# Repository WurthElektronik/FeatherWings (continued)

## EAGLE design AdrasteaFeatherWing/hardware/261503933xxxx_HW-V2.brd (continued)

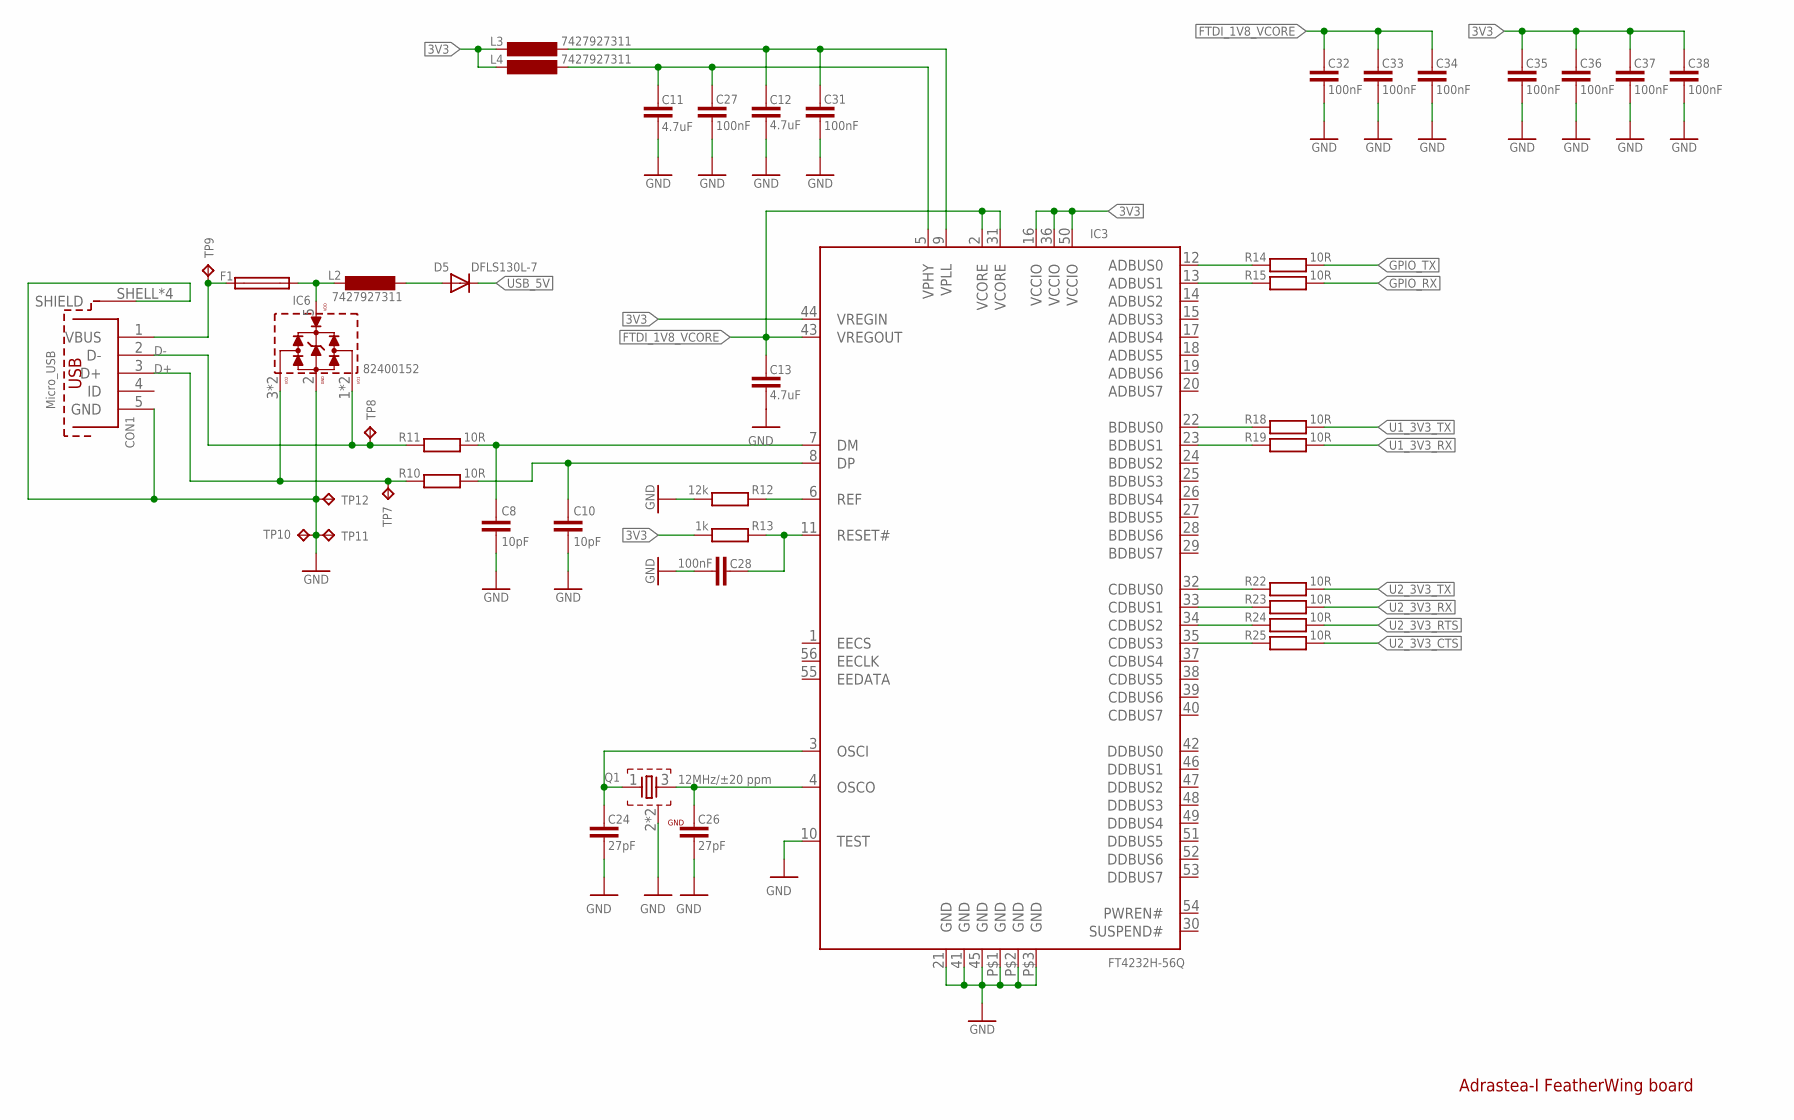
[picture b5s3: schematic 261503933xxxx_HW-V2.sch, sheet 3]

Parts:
C8, C10: 10pF; C0402_IPC
C11, C12, C13: 4.7uF; C0402_IPC
C24, C26: 27pF; C0402_IPC
C27, C28, C31, C32, C33, C34, C35, C36, C37, C38: 100nF; C0402_IPC
CON1: Micro_USB; 629105150521
D5: DFLS130L-7; SOD123_POWERDI
F1: ERB-RD1R50X; 0402
IC3: FT4232H-56Q; VQFN-56
IC6: 82400152; WE-TVS_SOT563
L2, L3, L4: 7427927311; L0402_WE-MK
Q1: 12MHz/±20 ppm; WE-XTAL_CFPX-180
R10, R11, R14, R15, R18, R19, R22, R23, R24, R25: 10R; R0402_IPC
R12: 12k; R0402_IPC
R13: 1k; R0402_IPC
TP7, TP8, TP9, TP10, TP11, TP12: TP15R

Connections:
3V3: C35.2, C36.2, C37.2, C38.2, IC3.16 (VCCIO), IC3.36 (VCCIO), IC3.44 (VREGIN), IC3.50 (VCCIO), L3.P$2 (2), L4.P$2 (2), R13.1; also elsewhere on the board
D+: CON1.3 (D+), IC6.3 (I/O2), IC6.4 (I/O2), R10.1, TP7.P$1
D-: CON1.2 (D-), IC6.1 (I/O1), IC6.6 (I/O1), R11.2, TP8.P$1
FTDI_1V8_VCORE: C13.1, C32.2, C33.2, C34.2, IC3.2 (VCORE), IC3.31 (VCORE), IC3.43 (VREGOUT)
FTDI_CTS#_CH-C: IC3.35 (CDBUS3), R25.1
FTDI_RESET: C28.2, IC3.11 (RESET#), R13.2
FTDI_RTS#_CH-C: IC3.34 (CDBUS2), R24.1
FTDI_RXD_CH-A: IC3.13 (ADBUS1), R15.1
FTDI_RXD_CH-B: IC3.23 (BDBUS1), R19.1
FTDI_RXD_CH-C: IC3.33 (CDBUS1), R23.1
FTDI_TXD_CH-A: IC3.12 (ADBUS0), R14.1
FTDI_TXD_CH-B: IC3.22 (BDBUS0), R18.1
FTDI_TXD_CH-C: IC3.32 (CDBUS0), R22.1
GND: C8.1, C10.1, C11.2, C12.2, C13.2, C24.1, C26.1, C27.1, C28.1, C31.1, C32.1, C33.1, C34.1, C35.1, C36.1, C37.1, C38.1, CON1.5 (GND), CON1.SHELL (SHIELD), CON1.SHELL1 (SHIELD), CON1.SHELL2 (SHIELD), CON1.SHELL3 (SHIELD), IC3.10 (TEST), IC3.21 (GND), IC3.41 (GND), IC3.45 (GND), IC3.P$1 (GND), IC3.P$2 (GND), IC3.P$3 (GND), IC6.2 (GND), Q1.2 (GND), Q1.4 (GND), R12.1, TP10.P$1, TP11.P$1, TP12.P$1; also elsewhere on the board
GPIO_RX: R15.2; also elsewhere on the board
GPIO_TX: R14.2; also elsewhere on the board
unnamed: C8.2, IC3.7 (DM), R11.1
unnamed: C10.2, IC3.8 (DP), R10.2
unnamed: D5.A, L2.P$1 (1)
unnamed: F1.2, IC6.5 (VDD), L2.P$2 (2)
unnamed: C11.1, C27.2, IC3.5 (VPHY), L4.P$1 (1)
unnamed: C12.1, C31.2, IC3.9 (VPLL), L3.P$1 (1)
unnamed: IC3.6 (REF), R12.2
unnamed: C24.2, IC3.3 (OSCI), Q1.1
unnamed: C26.2, IC3.4 (OSCO), Q1.3 (2)
U1_3V3_RX: R19.2; also elsewhere on the board
U1_3V3_TX: R18.2; also elsewhere on the board
U2_3V3_CTS: R25.2; also elsewhere on the board
U2_3V3_RTS: R24.2; also elsewhere on the board
U2_3V3_RX: R23.2; also elsewhere on the board
U2_3V3_TX: R22.2; also elsewhere on the board
USB_5V: D5.K (C); also elsewhere on the board
VBUS: CON1.1 (VBUS), F1.1, TP9.P$1

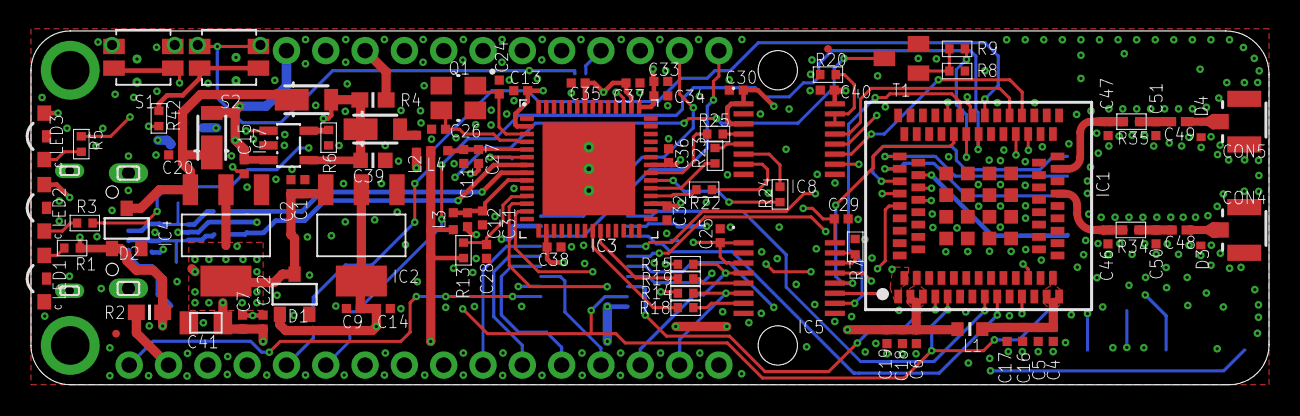
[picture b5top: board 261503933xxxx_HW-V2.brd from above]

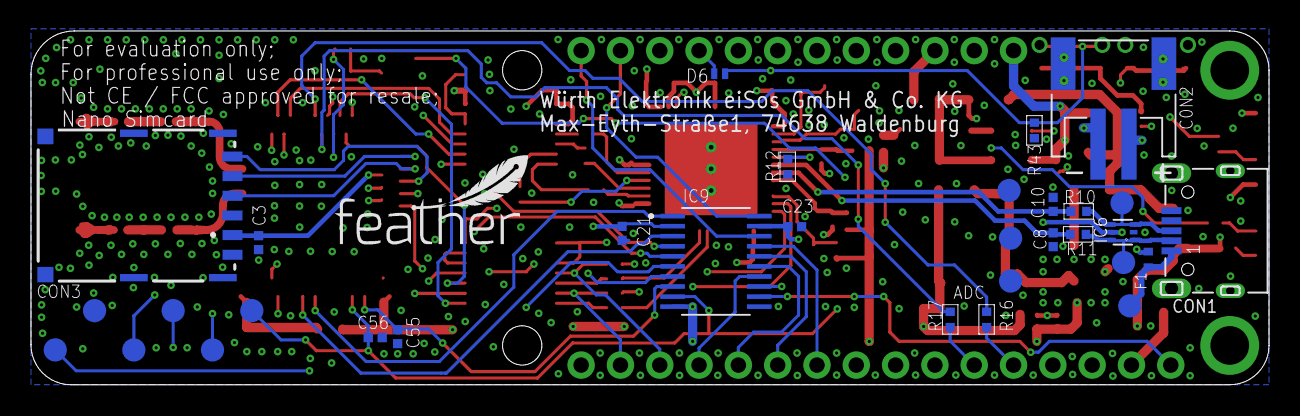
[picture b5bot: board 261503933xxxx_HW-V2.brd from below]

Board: 4 copper layers, 80.0 x 22.9 mm, 127 parts (33 on the bottom side), 91 nets.

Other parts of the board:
U$4: FEATHER_12MM

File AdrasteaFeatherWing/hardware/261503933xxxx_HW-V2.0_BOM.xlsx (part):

Part | Value | NR | MANUFACTURER | COMMENT | Device | Package | Description | CCH-TYP | COMMENT2 | DATASHEET-URL | DESCRIPTION3 | GENDER | GERDER | HEIGHT | HERSTELLER | ILEAK | ISAT | Spalte4 | MANUFACTURER2 | MAT | MF | MOUNT | MP | Spalte5 | NR2 | P | PACK | PACKAGE6 | PART-NUMBER | PINS | PRICE | RDC | SPG | TEMP | TOL | TYPE | VALUE | VCH-TYP | VESD-AIR | VESD-CONTACT | Z
C0N2 | LiPoLy-Plug | 1769 | Adafruit |  | JST_2PIN | JST-PH-2-SMT-RA-ADRASTEA-ANGEPASST | JST 2-Pin Connectors of various flavors |  |  |  |  |  |  | 9mm |  |  |  |  |  |  |  |  |  |  |  |  | SMT
C1 | 100nF | 885012205037 | Würth Elektronik |  | C0402_IPC | C0402_IPC |  |  |  |  |  |  |  | 0.5mm |  |  |  |  |  | X7R |  |  |  |  |  |  | 402 |  |  |  |  |  | 16V |  | 0.1
C10 | 10pF | 885012005055 | Würth Elektronik |  | C10PF0402_IPC | C0402_IPC |  |  |  |  |  |  |  | 0.5mm |  |  |  |  |  | NP0 |  |  |  |  |  |  | 402 |  |  |  |  |  | 50V |  | 0.05
C11 | 4.7uF | 885012105008 | Würth Elektronik |  | C4.7UF0402_IPC | C0402_IPC |  |  |  |  |  |  |  | 0.5mm |  |  |  |  |  | X5R |  |  |  |  |  |  | 402 |  |  |  |  |  | 6.3V |  | 0.2
C12 | 4.7uF | 885012105008 | Würth Elektronik |  | C4.7UF0402_IPC | C0402_IPC |  |  |  |  |  |  |  | 0.5mm |  |  |  |  |  | X5R |  |  |  |  |  |  | 402 |  |  |  |  |  | 6.3V |  | 0.2
C13 | 4.7uF | 885012105008 | Würth Elektronik |  | C4.7UF0402_IPC | C0402_IPC |  |  |  |  |  |  |  | 0.5mm |  |  |  |  |  | X5R |  |  |  |  |  |  | 402 |  |  |  |  |  | 6.3V |  | 0.2
C14 | 100nF | 885012205037 | Würth Elektronik |  | C0402_IPC | C0402_IPC |  |  |  |  |  |  |  | 0.5mm |  |  |  |  |  | X7R |  |  |  |  |  |  | 402 |  |  |  |  |  | 16V |  | 0.1
C15 | 10uF | 885012105020 | Würth Elektronik |  | C10UF0402_IPC | C0402_IPC |  |  |  |  |  |  |  | 0.5mm |  |  |  |  |  | X5R |  |  |  |  |  |  | 402 |  |  |  |  |  | 6.3V | -55 to +85°c | 0.2
C16 | 10uF | 885012105020 | Würth Elektronik |  | C0402_IPC | C0402_IPC |  |  |  |  |  |  |  | 0.5mm |  |  |  |  |  | X5R | 0.2 |  |  |  |  |  | 402 |  |  |  |  |  | 6,3V |  | 0.2
C17 | 1uF | 885012105012 | Würth Elektronik |  | C1UF0402_IPC | C0402_IPC |  |  |  |  |  |  |  | 0.5mm |  |  |  |  |  | X5R |  |  |  |  |  |  | 402 |  |  |  |  |  | 10V |  | 0.2
C18 | 10uF | 885012105020 | Würth Elektronik |  | C0402_IPC | C0402_IPC |  |  |  |  |  |  |  | 0.5mm |  |  |  |  |  | X5R | 0.2 |  |  |  |  |  | 402 |  |  |  |  |  | 6,3V |  | 0.2
C19 | 10uF | 885012105020 | Würth Elektronik |  | C0402_IPC | C0402_IPC |  |  |  |  |  |  |  | 0.5mm |  |  |  |  |  | X5R | 0.2 |  |  |  |  |  | 402 |  |  |  |  |  | 6,3V |  | 0.2
C2 | 1uF | 885012105012 | Würth Elektronik |  | C1UF0402_IPC | C0402_IPC |  |  |  |  |  |  |  | 0.5mm |  |  |  |  |  | X5R |  |  |  |  |  |  | 402 |  |  |  |  |  | 10V |  | 0.2
C20 | 100nF | 885012205037 | Würth Elektronik |  | C0402_IPC | C0402_IPC |  |  |  |  |  |  |  | 0.5mm |  |  |  |  |  | X7R |  |  |  |  |  |  | 402 |  |  |  |  |  | 16V |  | 0.1
C21 | 100nF | 885012205037 | Würth Elektronik |  | C0402_IPC | C0402_IPC |  |  |  |  |  |  |  | 0.5mm |  |  |  |  |  | X7R |  |  |  |  |  |  | 402 |  |  |  |  |  | 16V |  | 0.1
C22 | 100nF | 885012205037 | Würth Elektronik |  | C0402_IPC | C0402_IPC |  |  |  |  |  |  |  | 0.5mm |  |  |  |  |  | X7R |  |  |  |  |  |  | 402 |  |  |  |  |  | 16V |  | 0.1
C23 | 100nF | 885012205037 | Würth Elektronik |  | C0402_IPC | C0402_IPC |  |  |  |  |  |  |  | 0.5mm |  |  |  |  |  | X7R |  |  |  |  |  |  | 402 |  |  |  |  |  | 16V |  | 0.1
C24 | 27pF | CL05C270JB5NNNC | Samsung |  | C27P0402_IPC | C0402_IPC |  |  |  |  |  |  |  | 0.5mm |  |  |  |  |  | C0G |  |  |  |  |  |  | 402 |  |  |  |  |  | 50V |  | 0.05
C25 | 100nF | 885012205037 | Würth Elektronik |  | C0402_IPC | C0402_IPC |  |  |  |  |  |  |  | 0.5mm |  |  |  |  |  | X7R |  |  |  |  |  |  | 402 |  |  |  |  |  | 16V |  | 0.1
C26 | 27pF | CL05C270JB5NNNC | Samsung |  | C27P0402_IPC | C0402_IPC |  |  |  |  |  |  |  | 0.5mm |  |  |  |  |  | C0G |  |  |  |  |  |  | 402 |  |  |  |  |  | 50V |  | 0.05
C27 | 100nF | 885012205037 | Würth Elektronik |  | C0402_IPC | C0402_IPC |  |  |  |  |  |  |  | 0.5mm |  |  |  |  |  | X7R |  |  |  |  |  |  | 402 |  |  |  |  |  | 16V |  | 0.1
C28 | 100nF | 885012205037 | Würth Elektronik |  | C0402_IPC | C0402_IPC |  |  |  |  |  |  |  | 0.5mm |  |  |  |  |  | X7R |  |  |  |  |  |  | 402 |  |  |  |  |  | 16V |  | 0.1
C29 | 100nF | 885012205037 | Würth Elektronik |  | C0402_IPC | C0402_IPC |  |  |  |  |  |  |  | 0.5mm |  |  |  |  |  | X7R |  |  |  |  |  |  | 402 |  |  |  |  |  | 16V |  | 0.1
C3 | 100nF | 885012205037 | Würth Elektronik |  | C100NF0402_IPC | C0402_IPC |  |  |  |  |  |  |  | 0.5mm |  |  |  |  |  | X7R |  |  |  |  |  |  | 402 |  |  |  |  |  | 16V | -55 to +125°C | 0.1
C30 | 100nF | 885012205037 | Würth Elektronik |  | C0402_IPC | C0402_IPC |  |  |  |  |  |  |  | 0.5mm |  |  |  |  |  | X7R |  |  |  |  |  |  | 402 |  |  |  |  |  | 16V |  | 0.1
C31 | 100nF | 885012205037 | Würth Elektronik |  | C0402_IPC | C0402_IPC |  |  |  |  |  |  |  | 0.5mm |  |  |  |  |  | X7R |  |  |  |  |  |  | 402 |  |  |  |  |  | 16V |  | 0.1
C32 | 100nF | 885012205037 | Würth Elektronik |  | C0402_IPC | C0402_IPC |  |  |  |  |  |  |  | 0.5mm |  |  |  |  |  | X7R |  |  |  |  |  |  | 402 |  |  |  |  |  | 16V |  | 0.1
C33 | 100nF | 885012205037 | Würth Elektronik |  | C0402_IPC | C0402_IPC |  |  |  |  |  |  |  | 0.5mm |  |  |  |  |  | X7R |  |  |  |  |  |  | 402 |  |  |  |  |  | 16V |  | 0.1
C34 | 100nF | 885012205037 | Würth Elektronik |  | C0402_IPC | C0402_IPC |  |  |  |  |  |  |  | 0.5mm |  |  |  |  |  | X7R |  |  |  |  |  |  | 402 |  |  |  |  |  | 16V |  | 0.1
C35 | 100nF | 885012205037 | Würth Elektronik |  | C0402_IPC | C0402_IPC |  |  |  |  |  |  |  | 0.5mm |  |  |  |  |  | X7R |  |  |  |  |  |  | 402 |  |  |  |  |  | 16V |  | 0.1
C36 | 100nF | 885012205037 | Würth Elektronik |  | C0402_IPC | C0402_IPC |  |  |  |  |  |  |  | 0.5mm |  |  |  |  |  | X7R |  |  |  |  |  |  | 402 |  |  |  |  |  | 16V |  | 0.1
C37 | 100nF | 885012205037 | Würth Elektronik |  | C0402_IPC | C0402_IPC |  |  |  |  |  |  |  | 0.5mm |  |  |  |  |  | X7R |  |  |  |  |  |  | 402 |  |  |  |  |  | 16V |  | 0.1
C38 | 100nF | 885012205037 | Würth Elektronik |  | C0402_IPC | C0402_IPC |  |  |  |  |  |  |  | 0.5mm |  |  |  |  |  | X7R |  |  |  |  |  |  | 402 |  |  |  |  |  | 16V |  | 0.1
C39 | 10uF | 885012106031 | Wurth Elektronik |  | C1UF0603_IPC | C0603_IPC |  |  |  |  |  |  |  | 0.8mm |  |  |  |  |  | X5R |  |  |  |  |  |  | 603 |  |  |  |  |  | 25V |  | 0.1
C4 | 100nF | 885012205037 | Würth Elektronik |  | C0402_IPC | C0402_IPC |  |  |  |  |  |  |  | 0.5mm |  |  |  |  |  | X7R |  |  |  |  |  |  | 402 |  |  |  |  |  | 16V |  | 0.1
C40 | 100nF | 885012205037 | Würth Elektronik |  | C0402_IPC | C0402_IPC |  |  |  |  |  |  |  | 0.5mm |  |  |  |  |  | X7R |  |  |  |  |  |  | 402 |  |  |  |  |  | 16V |  | 0.1
C41 | 47µF | 885012107006 | Wurth Elektronik |  | C47UF0805 | C0805 |  |  |  |  |  |  |  | 1.25mm |  |  |  |  |  | X7R |  |  |  |  |  |  | 805 |  |  |  |  |  | 6.3V |  | 0.2
C46 | n.m. | n.m. | n.m. |  | C0402_IPC | C0402_IPC |  |  |  |  |  |  |  | 0.5mm |  |  |  |  |  |  |  |  |  |  |  |  | 402
C47 | n.m. | n.m. | n.m. |  | C0402_IPC | C0402_IPC |  |  |  |  |  |  |  | 0.5mm |  |  |  |  |  |  |  |  |  |  |  |  | 402
C48 | 100pF | 885012005061 | Würth Elektronik |  | C100PF0402_IPC | C0402_IPC |  |  |  |  |  |  |  | 0.5mm |  |  |  |  |  | NP0 |  |  |  |  |  |  | 402 |  |  |  |  |  | 50V |  | 0.05
C49 | 100pF | 885012005061 | Würth Elektronik |  | C0402_IPC | C0402_IPC |  |  |  |  |  |  |  | 0.5mm |  |  |  |  |  | NP0 |  |  |  |  |  |  | 402 |  |  |  |  |  | 50V |  | 0.05
C5 | 10uF | 885012105020 | Würth Elektronik |  | C0402_IPC | C0402_IPC |  |  |  |  |  |  |  | 0.5mm |  |  |  |  |  | X5R | 0.2 |  |  |  |  |  | 402 |  |  |  |  |  | 6,3V |  | 0.2
C50 | n.m. | n.m. | n.m. |  | C0402_IPC | C0402_IPC |  |  |  |  |  |  |  | 0.5mm |  |  |  |  |  |  |  |  |  |  |  |  | 402
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
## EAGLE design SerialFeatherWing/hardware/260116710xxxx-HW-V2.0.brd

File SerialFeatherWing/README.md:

# Serial FeatherWing

## Introduction

The Würth Elektronik eiSos Serial bridge FeatherWing is a development board that acts as an bridge between UART and RS232/RS485/RS422. It is fully compatible to the popular [Adafruit](https://www.adafruit.com/) [Feather line](https://www.adafruit.com/feather) of development boards and can be used as plug-and-play solution to connect any D-SUB9 interfaced device to the Feather ecosystem.

This FeatherWing acts as a bridge between legacy RS232/RS485 devices and modern wired/wireless digital interfaces
### Key Features

* 3V3 logic level UART interface on the Feather pin header.
* Support to 5V logic level
* RS232 with and without flow control
* Full and half duplex RS485
* Double throw slider to switch between RS232 and RS485

This repository contains the [Eagle](https://www.autodesk.com/products/eagle/overview) design files for the MagI³C Power FeatherWing [PCB](hardware).

Feel free to check our [YouTube channel](https://www.youtube.com/user/WuerthElektronik/videos) for video tutorials, hands-ons and webinars relating to our products.

## Hardware

### Description

The Serial FeatherWing was designed with rapid prototyping in mind. Being fully compatible with the Adafruit ecosystem, this FeatherWing gives the user the flexibility to choose the preferred host microcontroller. The inherent modularity of the ecosystem allows the FeatherWing to be easily integrated into any project.

### Connectors

#### CON1
This is a standard D-subminiature Male connector. The pinout for different modes of operation are as described in the table below.

|Pin | RS232 | RS485(Full Duplex)| RS485 (Half Duplex)|
|----|----------|-------------|------|
|1| Not connected |Not connected| Not connected|
|2 |RX |RX+| Not connected|
3| TX |TX- | D-|
|4 |Not connected| Not connected| Not connected|
|5 |GND |GND |GND|
|6 |Not connected| Not connected |Not connected|
|7 |RTS| TX+ |D+|
|8 |CTS |RX-| Not connected|
|9 |Not connected| Not connected |Not connected|

#### Feather Connector
This is the standard set of connectors that is used across the Feather ecosystem. The table below describes the functions of each of the 28 pins as applicable to this FeatherWing.

| Pin number | Pin name | Function |
| ------- | ------- |----------------|
|   1          |<span style="text-decoration:overline">RST</span> | Not connected|
|    2          | 3V3| 3.3 V power supply|
|    3          | AREF| Not connected|
|    4          | GND| Ground|
|    5          | A0| Not connected|
|    6          | A1| Not connected|
|    7          | A2| Not connected|
|    8          | A3| Not connected|
|    9          | A4| Not connected|
|    10         | A5| Not connected|
|    11         | SCK| Not connected|
|    12         | MOSI| Not connected|
|    13         | MISO| Not connected|
|    14         | U0RX| Connected to UART TX(RS232/RS485 TX)|
|    15         | U0TX| Connected to UART RX(RS232/RS485 RX)|
|    16         | NC| Not connected|

| Pin number | Pin name | Function |
| ------- | ------- |----------------|
|    17         | SDA| Not connected|
|    18         | SCL| Not connected|
|    19         | 5| Not connected|
|    20         | 6| Not connected|
|    21         | 9| Not connected|
|    22         | U1TX|(optional) Connected to UART RX(RS232 RS485 RX)|
|    23         | U1RX|(optional) Connected to UART TX(RS232/RS485 TX)|
|    24         | 12| Not connected|
|    25         | 13| Not connected|
|    26         | 5V| 5 V Power supply|
|    27         | EN| Not connected|
|    28         | VBAT| Not connected| 

### Switches

#### Switch S1

This sliding switch can be used to select between the two input signal options, RS232 or RS485.
|Position| Mode|
|--------|------|
|Top (Away from D-SUB 9 connector)| RS232|
|Bottom (Towards D-SUB 9 connector)| RS485|

#### Switch S2

This sliding switch determines if the RX/TX lines are crossed to connect directly to another UART peripheral such as a radio module.
|Position| Mode|
|--------|------|
|Top (Away from D-SUB 9 connector)| TX and RX are crossed|
|Bottom (Towards D-SUB 9 connector)| TX and RX are not crossed|

### Jumpers

#### Jumper JP1

This jumper enables switching between half and full duplex modes as well as enabling/disabling the slew rate.

|Connection| Mode|
|--------|-------|
|1-3| Full duplex|
|3-5|Half duplex|

|Connection| Mode|
|--------|-------|
|2-4 |Slew rate enabled|
|4-6 |Slew rate disabled|

#### Jumper JP2

This jumper enables switching between the UART0 and UART1 on the feather connector.

|Connection| Mode|
|--------|-------|
|1-3 and 2-4| UART0|
|3-5 and 4-6|UART1|

#### Jumper JP3
This jumper enables connecting the flow control pins to the GPIOs on the feather connector

|Connection| Mode|
|--------|-------|
|1-2| RTS/DE connected to GPIO12|
|3-4|CTS conected to GPIO13|

### Schematics
The hardware design files including the schematics can be found in the [hardware folder](hardware).

### DISCLAIMER:
THE USE OF THE WÜRTH ELEKTRONIK EISOS DESIGN EXAMPLE / REFERENCE DESIGN IS ENTIRELY AT YOUR OWN RISK. IT IS YOUR SOLE RESPONSIBILITY TO IMPLEMENT THE DESIGN EXAMPLE / REFERENCE DESIGN WITH ALL TECHNICAL AND REGULATORY REQUIREMENTS IN YOUR APPLICATION. IT IS ALSO YOUR RESPONSIBILITY TO VERIFY THE FUNCTION AND PERFORMANCE OF YOUR DESIGN IN YOUR OWN PARTICULAR ENGINEERING AND PRODUCT ENVIRONMENT AND YOU ASSUME THE ENTIRE RISK OF DOING SO OR FAILING TO DO SO. THE WÜRTH ELEKTRONIK EISOS DESIGN EXAMPLE / REFERENCE DESIGN IS PROVIDED ON AN "AS IS" OR "AS AVAILABLE" BASIS, WITHOUT ANY WARRANTIES OF ANY KIND AND WÜRTH ELEKTRONIK EISOS DISCLAIMS ANY WARRANTIES EXPRESS OR IMPLIED, INCLUDING WITHOUT LIMITATION THE MERCHANTABILITY OR FITNESS FOR A PARTICULAR PURPOSE, USAGE OR THE NON-INFRINGEMENT OF THIRD PARTIES’ INTELLECTUAL PROPERTY RIGHTS. NO LICENSE IS GRANTED TO ANY INTELLECTUAL PROPERTY RIGHT BY WÜRTH ELEKTRONIK EISOS OR ANY THIRD PARY. UNDER NO CIRCUMSTANCES SHALL WÜRTH ELEKTRONIK EISOS BE LIABLE FOR DAMAGES INCURRED BY REASON OF OTHER SERVICES OR PRODUCTS RECEIVED THROUGH OR ADVERTISED IN CONNECTION WITH THE WÜRTH ELEKTRONIK EISOS SITE OR THE WÜRTH ELEKTRONIK EISOS DESIGN EXAMPLE / REFERENCE DESIGN. THE WÜRTH ELEKTRONIK EISOS DESIGN EXAMPLE / REFERENCE DESIGN IS SUBJECT TO CHANGE WITHOUT NOTICE.

## Software
Serial bridge FeatherWing **software examples** can be found in the [software folder](software).

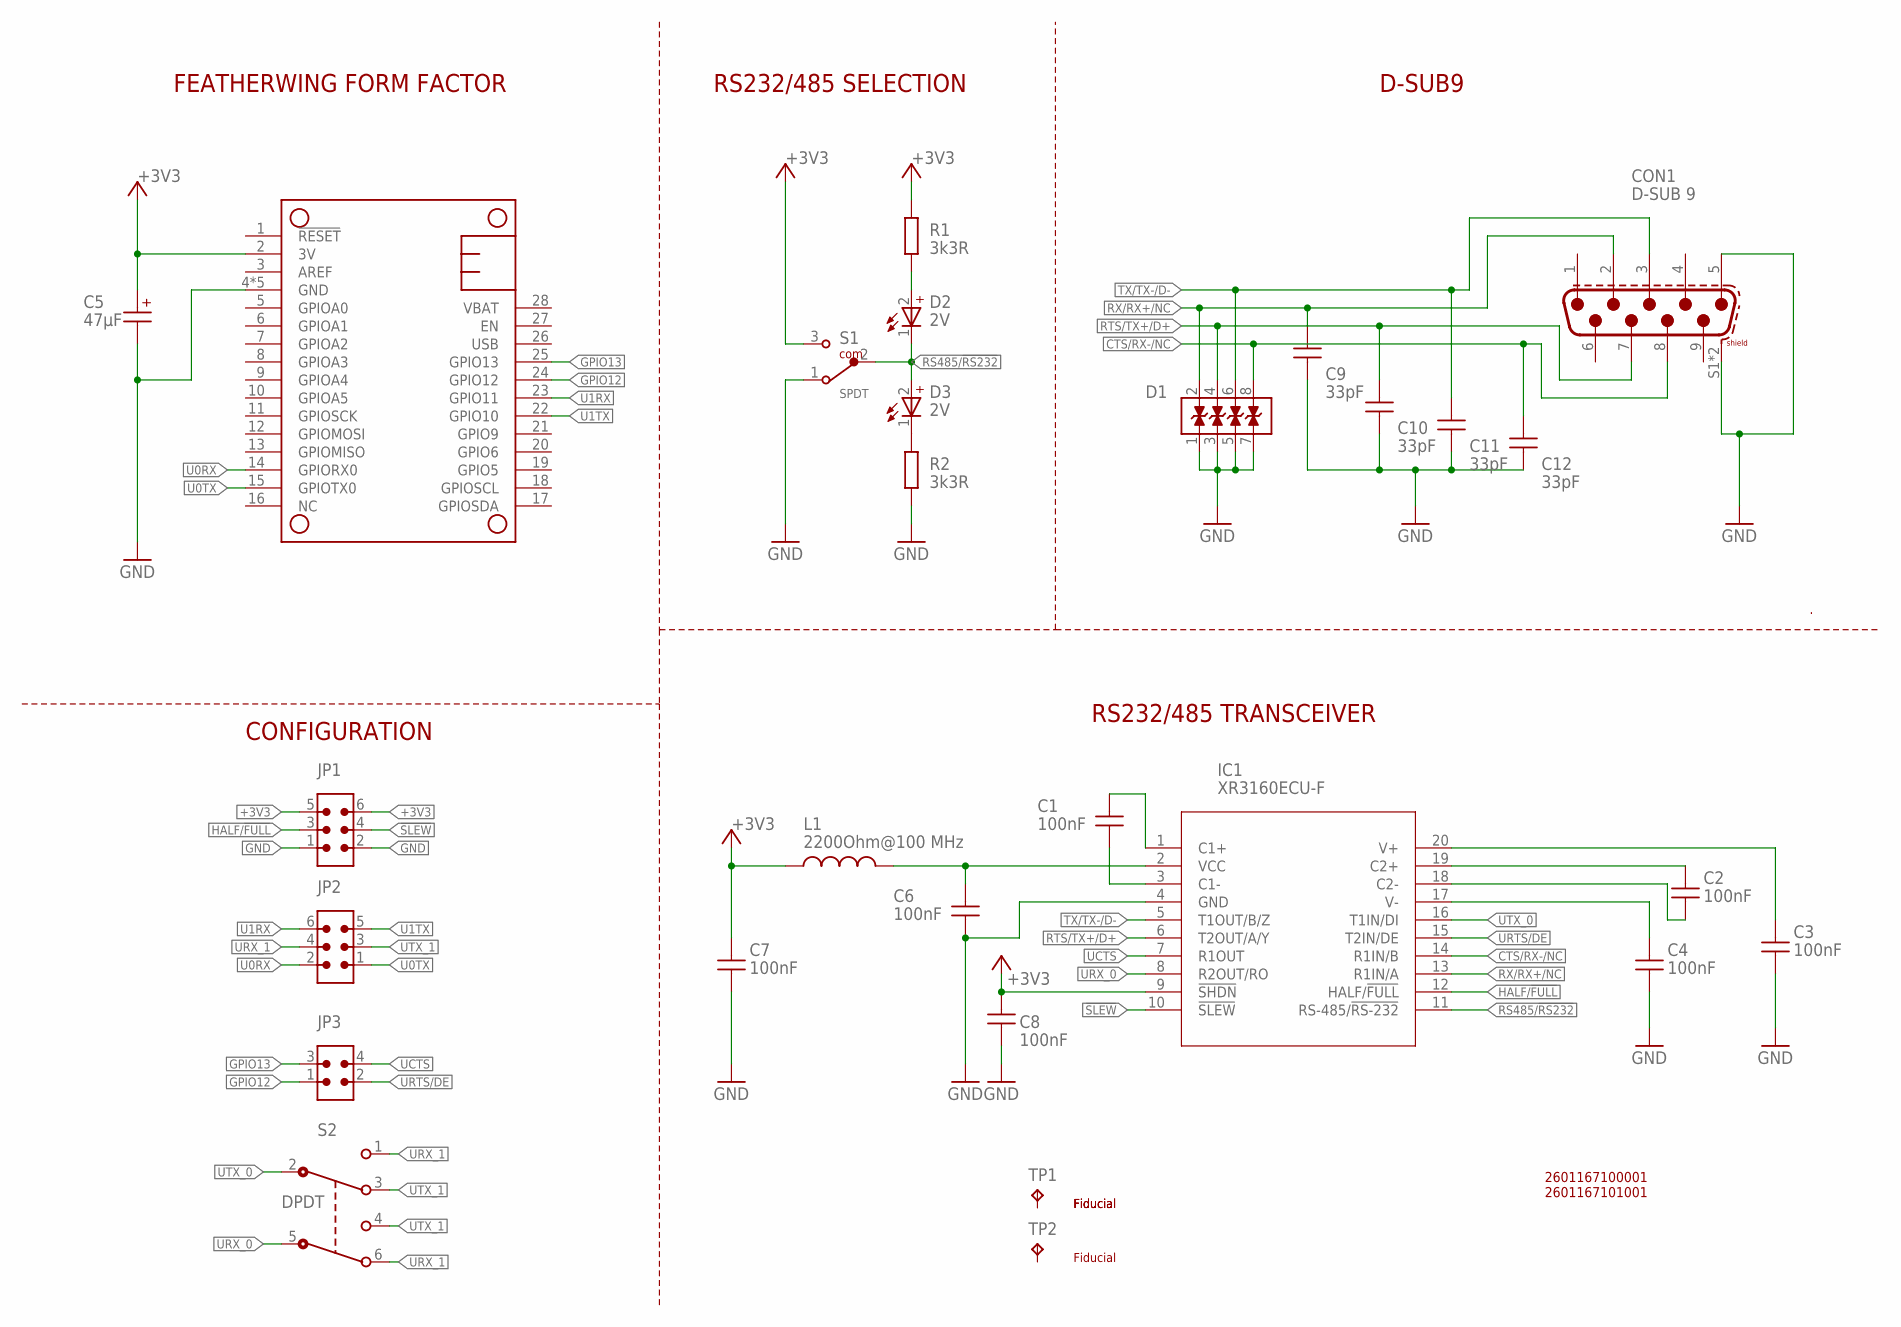
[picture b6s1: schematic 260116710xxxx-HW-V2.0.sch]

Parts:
C1, C2, C3, C4, C6, C7, C8: 100nF; WCAP-CSGP_0603_W
C5: 47µF; WCAP-AS5H_5X5.5(DXL)
C9, C10, C11, C12: 33pF; WCAP-CSGP_0603_W
CON1: D-SUB 9; 618009231221
D1: 18V; WE-VEA_0612
D2, D3: 2V; WL-SMCW_0603
IC1: XR3160ECU-F; SSOP-20
JP1, JP2: 61300621121
JP3: 61300421121
L1: 2200Ohm@100 MHz; WE-CBF_0603(W=2.2)
MS1: FEATHERWING_WIDE; PART-NUMBER 2830
R1, R2: 3k3R; R0603
S1: SPDT; 450404015514
S2: DPDT; 452403012014
TP1, TP2: TPB1,27; B1,27

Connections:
!SLEW: IC1.10 (!SLEW), JP1.4
+3V3: C5.1 (+), C7.2, C8.2, IC1.9 (!SHDN), JP1.5, JP1.6, L1.2, MS1.2 (3V), R1.1, S1.3
CTS/RX-/NC: C12.1, CON1.8, D1.8 (5), IC1.14 (R1IN/B)
GND: C3.1, C4.1, C5.2 (-), C6.1, C7.1, C8.1, C9.2, C10.2, C11.2, C12.2, CON1.5, CON1.S1 (SHIELD), CON1.S2 (SHIELD), D1.1, D1.3 (2), D1.5 (3), D1.7 (4), IC1.4 (GND), JP1.1, JP1.2, MS1.4 (GND), MS1.GND@0 (GND), MS1.GND@1 (GND), MS1.GND@2 (GND), MS1.GND@3 (GND), R2.1, S1.1
GPIO12: JP3.1, MS1.24 (GPIO12)
GPIO13: JP3.3, MS1.25 (GPIO13)
HALF/!FULL: IC1.12 (HALF/!FULL), JP1.3
unnamed: D3.1 (-), R2.2
unnamed: D2.2 (+), R1.2
unnamed: C1.2, IC1.1 (C1+)
unnamed: C1.1, IC1.3 (C1-)
unnamed: C6.2, IC1.2 (VCC), L1.1
unnamed: C2.2, IC1.19 (C2+)
unnamed: C2.1, IC1.18 (C2-)
unnamed: C3.2, IC1.20 (V+)
unnamed: C4.2, IC1.17 (V-)
RS485/!RS232: D2.1 (-), D3.2 (+), IC1.11 (RS-485/!RS-232), S1.2
RTS/TX+/D+: C10.1, CON1.7, D1.4 (7), IC1.6 (T2OUT/A/Y)
RX/RX+/NC: C9.1, CON1.2, D1.2 (8), IC1.13 (R1IN/A)
TX/TX-/D-: C11.1, CON1.3, D1.6, IC1.5 (T1OUT/B/Z)
U0RX: JP2.2, MS1.14 (GPIORX0)
U0TX: JP2.1, MS1.15 (GPIOTX0)
U1RX: JP2.6, MS1.23 (GPIO11)
U1TX: JP2.5, MS1.22 (GPIO10)
UCTS: IC1.7 (R1OUT), JP3.4
URTS/DE: IC1.15 (T2IN/DE), JP3.2
URX_0: IC1.8 (R2OUT/RO), S2.5
URX_1: JP2.4, S2.1, S2.6
UTX_0: IC1.16 (T1IN/DI), S2.2
UTX_1: JP2.3, S2.3, S2.4

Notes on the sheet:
FEATHERWING FORM FACTOR
CONFIGURATION
RS232/485 SELECTION
D-SUB9
RS232/485 TRANSCEIVER
2601167100001 2601167101001
Fiducial

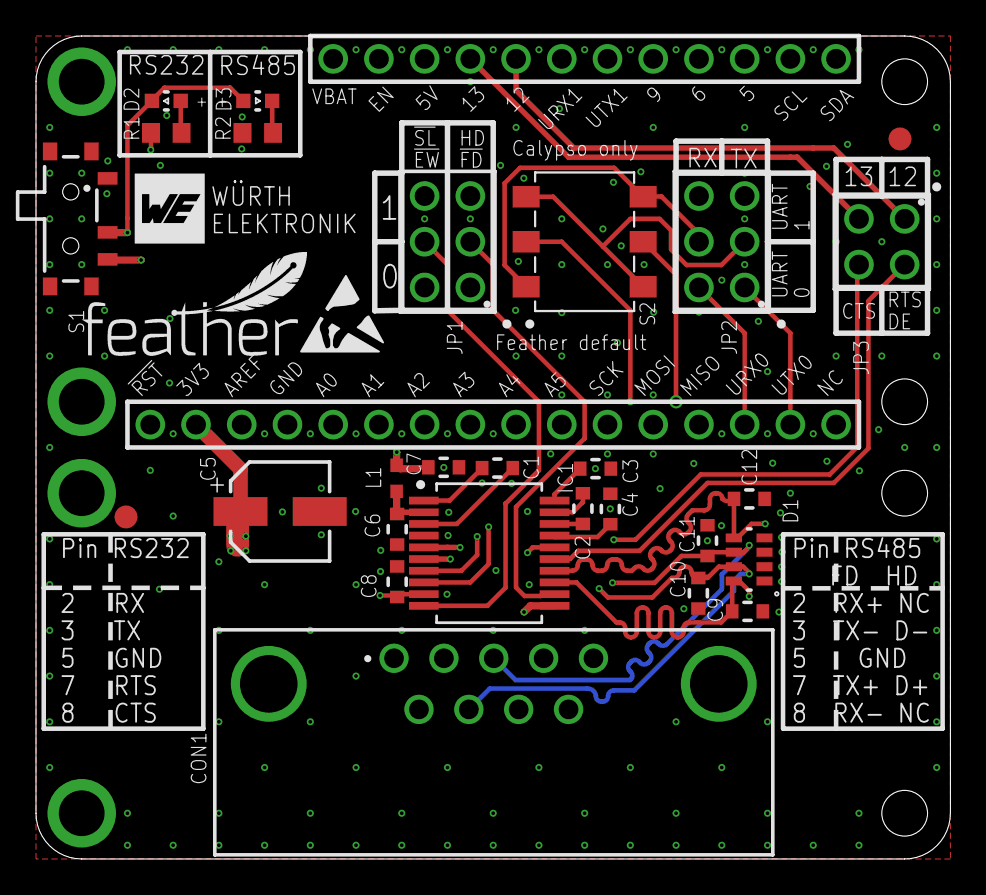
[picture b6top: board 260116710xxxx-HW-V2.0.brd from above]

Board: 4 copper layers, 50.8 x 45.7 mm, 32 parts (1 on the bottom side), 30 nets.

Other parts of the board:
U$1: WE-NEW_SKELETON_4MM
U$2: WE-NEW_SKELETON_8MM
U$4: ESD_5MM
U$5: FEATHER_12MM

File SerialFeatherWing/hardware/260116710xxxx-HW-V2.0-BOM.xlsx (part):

Part | Value | NR | MANUFACTURER | Device | Package | Description | ABSTRAHLWINKEL | CERAMIC-TYPE | CHANNELS | CHIP-TECHNOLOGY | COMMENT | COPYRIGHT | DATASHEET-URL | DF | DIAMETER | DIGI-KEY_PART_NUMBER_1 | EMITTING-COLOR | GENDER | HEIGHT | I-LEAK | I-RIPPLE | I-V-TYP | ILEAK | IR | IR2 | L | LAMDA-DOM-TYP | LAMDA-PEAK-TYP | MANUFACTURER_PART_NUMBER | MATES-WITH | MFR_NAME | PACK | OPERATING-TEMPERATURE | PACK | PACKAGING | PINS | PITCH | PQ | QMIN | QTY | RDC-MAX | RISO | ROWS | TECHNICAL-REFERENCE | TOL-VALUE | TP_SIGNAL_NAME | TYPE | V-F-TYP | VALUE | VR | WE-NUMBER | Z | Z-MAX | TOL
C1 | 100 nF | 885012206020 | Wurth Elektronik | WCAP-CSGP_0603_885012206020_10V(DC)_W | WCAP-CSGP_0603_W | WCAP-CSGP MLCCs 0603 |  | X7R Class II |  |  |  |  | https://www.we-online.com/catalog/datasheet/885012206020.pdf | 0.05 |  |  |  |  | 0.8mm |  |  |  |  |  |  |  |  |  |  |  |  | SMT | -55 °C up to +125 °C |  |  |  |  |  | - |  |  | 5GOhm |  | X7R0603104K010DFCT10000 | ±10% |  |  |  | 100 nF | 10V(DC)
C2 | 100 nF | 885012206020 | Wurth Elektronik | WCAP-CSGP_0603_885012206020_10V(DC)_W | WCAP-CSGP_0603_W | WCAP-CSGP MLCCs 0603 |  | X7R Class II |  |  |  |  | https://www.we-online.com/catalog/datasheet/885012206020.pdf | 0.05 |  |  |  |  | 0.8mm |  |  |  |  |  |  |  |  |  |  |  |  | SMT | -55 °C up to +125 °C |  |  |  |  |  | - |  |  | 5GOhm |  | X7R0603104K010DFCT10000 | ±10% |  |  |  | 100 nF | 10V(DC)
C3 | 100 nF | 885012206020 | Wurth Elektronik | WCAP-CSGP_0603_885012206020_10V(DC)_W | WCAP-CSGP_0603_W | WCAP-CSGP MLCCs 0603 |  | X7R Class II |  |  |  |  | https://www.we-online.com/catalog/datasheet/885012206020.pdf | 0.05 |  |  |  |  | 0.8mm |  |  |  |  |  |  |  |  |  |  |  |  | SMT | -55 °C up to +125 °C |  |  |  |  |  | - |  |  | 5GOhm |  | X7R0603104K010DFCT10000 | ±10% |  |  |  | 100 nF | 10V(DC)
C4 | 100 nF | 885012206020 | Wurth Elektronik | WCAP-CSGP_0603_885012206020_10V(DC)_W | WCAP-CSGP_0603_W | WCAP-CSGP MLCCs 0603 |  | X7R Class II |  |  |  |  | https://www.we-online.com/catalog/datasheet/885012206020.pdf | 0.05 |  |  |  |  | 0.8mm |  |  |  |  |  |  |  |  |  |  |  |  | SMT | -55 °C up to +125 °C |  |  |  |  |  | - |  |  | 5GOhm |  | X7R0603104K010DFCT10000 | ±10% |  |  |  | 100 nF | 10V(DC)
C5 | 47µF | 865230142003 | Wurth Elektronik | WCAP-AS5H_5X5.5_865230142003 | WCAP-AS5H_5X5.5(DXL) | WCAP-AS5H Aluminium Electrolytic Capacitors |  |  |  |  |  |  | https://www.we-online.com/catalog/datasheet/865230142003.pdf | 0.32 | 5mm |  |  |  |  | 3uA | 36mA |  |  |  |  | 5.5mm |  |  |  |  |  | SMT | -40 °C up to +105 °C |  |  |  |  |  |  |  |  |  |  | ASDC055470M6R3DVCTBE000 |  |  |  |  | 47 µF | 6.3V(DC) |  | 1.61882Ohm
C6 | 100 nF | 885012206020 | Wurth Elektronik | WCAP-CSGP_0603_885012206020_10V(DC)_W | WCAP-CSGP_0603_W | WCAP-CSGP MLCCs 0603 |  | X7R Class II |  |  |  |  | https://www.we-online.com/catalog/datasheet/885012206020.pdf | 0.05 |  |  |  |  | 0.8mm |  |  |  |  |  |  |  |  |  |  |  |  | SMT | -55 °C up to +125 °C |  |  |  |  |  | - |  |  | 5GOhm |  | X7R0603104K010DFCT10000 | ±10% |  |  |  | 100 nF | 10V(DC)
C7 | 100 nF | 885012206020 | Wurth Elektronik | WCAP-CSGP_0603_885012206020_10V(DC)_W | WCAP-CSGP_0603_W | WCAP-CSGP MLCCs 0603 |  | X7R Class II |  |  |  |  | https://www.we-online.com/catalog/datasheet/885012206020.pdf | 0.05 |  |  |  |  | 0.8mm |  |  |  |  |  |  |  |  |  |  |  |  | SMT | -55 °C up to +125 °C |  |  |  |  |  | - |  |  | 5GOhm |  | X7R0603104K010DFCT10000 | ±10% |  |  |  | 100 nF | 10V(DC)
C8 | 100 nF | 885012206020 | Wurth Elektronik | WCAP-CSGP_0603_885012206020_10V(DC)_W | WCAP-CSGP_0603_W | WCAP-CSGP MLCCs 0603 |  | X7R Class II |  |  |  |  | https://www.we-online.com/catalog/datasheet/885012206020.pdf | 0.05 |  |  |  |  | 0.8mm |  |  |  |  |  |  |  |  |  |  |  |  | SMT | -55 °C up to +125 °C |  |  |  |  |  | - |  |  | 5GOhm |  | X7R0603104K010DFCT10000 | ±10% |  |  |  | 100 nF | 10V(DC)
C9 | 33pF | 885012006035 | Wurth Elektronik | WCAP-CSGP_0603_885012006035_25V(DC)_W | WCAP-CSGP_0603_W | WCAP-CSGP MLCCs 0603 |  | NP0 Class I |  |  |  |  | https://www.we-online.com/catalog/datasheet/885012006035.pdf | - |  |  |  |  | 0.8mm |  |  |  |  |  |  |  |  |  |  |  |  | SMT | -55 °C up to +125 °C |  |  |  |  |  | 1000 |  |  | 10GOhm |  | NP00603330J025DFCT10000 | ±5% |  |  |  | 33 pF | 25V(DC)
C10 | 33pF | 885012006035 | Wurth Elektronik | WCAP-CSGP_0603_885012006035_25V(DC)_W | WCAP-CSGP_0603_W | WCAP-CSGP MLCCs 0603 |  | NP0 Class I |  |  |  |  | https://www.we-online.com/catalog/datasheet/885012006035.pdf | - |  |  |  |  | 0.8mm |  |  |  |  |  |  |  |  |  |  |  |  | SMT | -55 °C up to +125 °C |  |  |  |  |  | 1000 |  |  | 10GOhm |  | NP00603330J025DFCT10000 | ±5% |  |  |  | 33 pF | 25V(DC)
C11 | 33pF | 885012006035 | Wurth Elektronik | WCAP-CSGP_0603_885012006035_25V(DC)_W | WCAP-CSGP_0603_W | WCAP-CSGP MLCCs 0603 |  | NP0 Class I |  |  |  |  | https://www.we-online.com/catalog/datasheet/885012006035.pdf | - |  |  |  |  | 0.8mm |  |  |  |  |  |  |  |  |  |  |  |  | SMT | -55 °C up to +125 °C |  |  |  |  |  | 1000 |  |  | 10GOhm |  | NP00603330J025DFCT10000 | ±5% |  |  |  | 33 pF | 25V(DC)
C12 | 33pF | 885012006035 | Wurth Elektronik | WCAP-CSGP_0603_885012006035_25V(DC)_W | WCAP-CSGP_0603_W | WCAP-CSGP MLCCs 0603 |  | NP0 Class I |  |  |  |  | https://www.we-online.com/catalog/datasheet/885012006035.pdf | - |  |  |  |  | 0.8mm |  |  |  |  |  |  |  |  |  |  |  |  | SMT | -55 °C up to +125 °C |  |  |  |  |  | 1000 |  |  | 10GOhm |  | NP00603330J025DFCT10000 | ±5% |  |  |  | 33 pF | 25V(DC)
CON1 | D-SUB 9 | 618009231221 | Wurth Elektronik | 6180XX231221_618009231221 | 618009231221 | WR-DSUB 8.08 mm Male Angled PCB Connector w. Hex Screw |  |  |  |  |  |  | https://www.we-online.com/catalog/datasheet/618009231221.pdf |  |  |  |  | Male |  |  |  |  |  |  |  |  |  |  |  | WR-DSUB 10.30 mm Female Angled PCB Connector w/o Hex Screw /Female PCB Connecto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 |  | THT |  |  |  | 9 |  |  |  |  |  |  |  |  |  |  | Angled |  |  |  | 618009231221
D1 | 18V | 82380180121 | Wurth Elektronik | WE-VEA_0612_82380180121 | WE-VEA_0612 | WE-VEA ESD Suppressor-Array |  |  | 4 |  |  |  | https://katalog.we-online.de/pbs/datasheet/82380180121.pdf |  |  |  |  |  |  |  |  |  | 1uA |  |  |  |  |  |  |  |  | SMT |  |  |  |  |  |  |  |  |  | 10 MOhm |  |  |  |  |  |  | 18V
D2 | Amber | 150060AS75000 | Wurth Elektronik | WL-SMCW_0603_150060AS75000 | WL-SMCW_0603 | WL-SMCW SMT Mono-color Chip LED Waterclea | 140° |  |  | AlInGaP |  |  | https://www.we-online.com/catalog/datasheet/150060AS75000.pdf |  |  |  | Amber |  |  |  |  | 130mcd |  |  |  |  | 605nm | 610nm |  |  |  | SMT |  |  |  |  |  |  |  |  |  |  |  |  |  |  |  | 2V
D3 | Amber | 150060AS75000 | Wurth Elektronik | WL-SMCW_0603_150060AS75000 | WL-SMCW_0603 | WL-SMCW SMT Mono-color Chip LED Waterclea | 140° |  |  | AlInGaP |  |  | https://www.we-online.com/catalog/datasheet/150060AS75000.pdf |  |  |  | Amber |  |  |  |  | 130mcd |  |  |  |  | 605nm | 610nm |  |  |  | SMT |  |  |  |  |  |  |  |  |  |  |  |  |  |  |  | 2V
IC1 | XR3160ECU-F | XR3160ECU-F | MaxLinear | XR3160ECU-F | SSOP-20 |  |  |  |  |  |  | Copyright (C) 2021 Ultra Librarian. All rights reserved. |  |  |  | 1016-1966-5-ND |  |  |  |  |  |  |  |  |  |  |  |  | XR3160ECU-F |  | MaxLinear | SMT
JP1 | 61300621121 | 61300621121 | Wurth Elektronik | 6130XX21121_61300621121 | 61300621121 | WR-PHD 2.54 mm THT Dual Pin Header Jumper on PIN 1&3 and PIN 2&4 |  |  |  |  | Set jumper on PIN 1&3 and PIN 2&4 |  | https://www.we-online.com/catalog/datasheet/61300621121.pdf |  |  |  |  | Pin Header |  |  |  |  |  | 3A |  |  |  |  |  |  |  | THT |  |  | Bag | 6 | 2.54mm |  |  |  |  |  | Dual |  |  |  | Board Stacker |  | 61300621121
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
